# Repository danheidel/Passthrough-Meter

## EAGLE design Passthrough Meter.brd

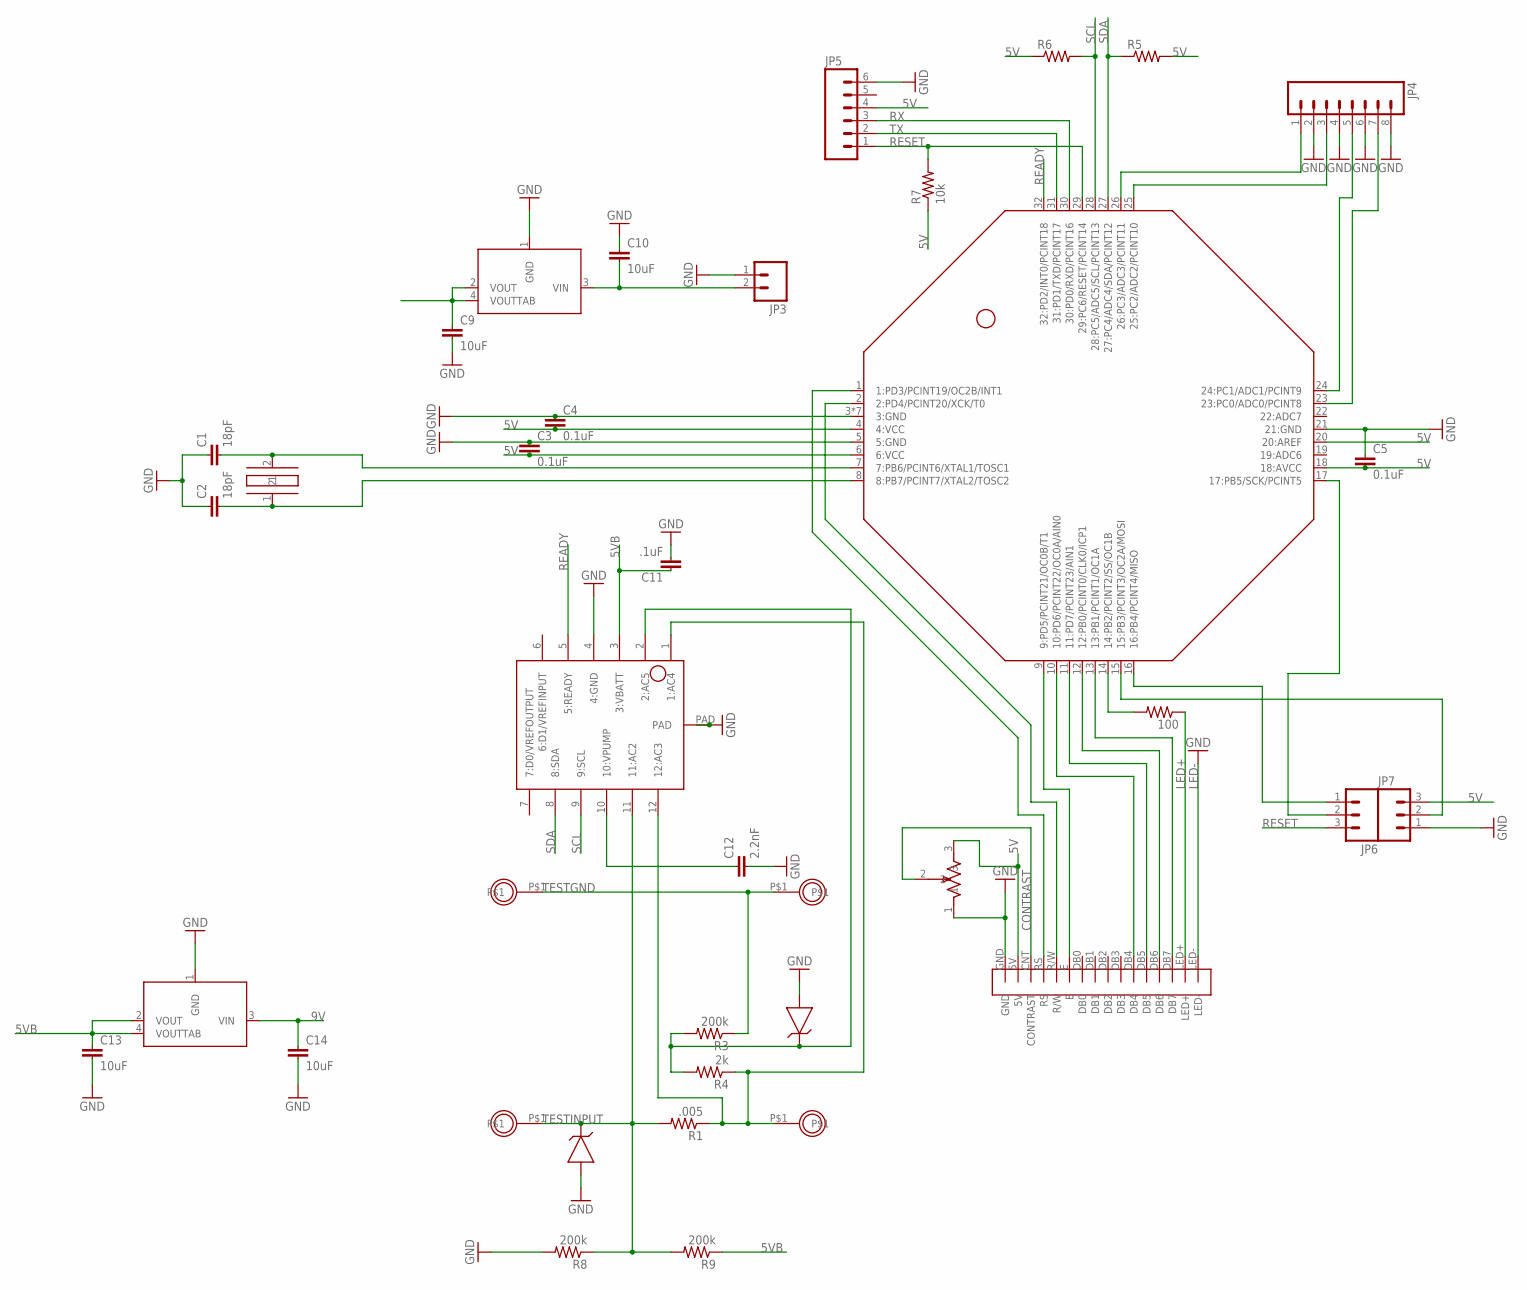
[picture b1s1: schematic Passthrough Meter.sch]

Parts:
100: RESISTOR; 0805
C1, C2: 18pF; 0603-CAP
C3, C4, C5: 0.1uF; 0805
C9, C10, C13, C14: 10uF; 1206
C11: .1uF; 0805
C12: 2.2nF; 0805
JP3: M02LOCK; 1X02_LOCK
JP4: M08LOCK; 1X08_LOCK
JP5: M06LOCK; 1X06_LOCK
JP6, JP7: M03LOCK; 1X03_LOCK
R1: .005; OAR5
R3, R8, R9: 200k; PRECISION-R1
R4: 2k; 0805
R5, R6: RESISTOR; 0805
R7: 10k; 0805
U$1: HC49US
U$3: ATMEGA328SMD-QFN; QFN-32
U$4: SX8723; MPLD-W-12-4X4
U$5, U$15: ZENER_DIODE-SOD-323; SOD-323
U$6: TRIMPOTTC33X-2; TC33X-2
U$7, U$8, U$9, U$10: THROUGH_HOLE-3MM; THROUGH_HOLE_2.2MM
U$13, U$14: 5V-LDO-ZLDO1117; ZLDO1117
U$16: LCD

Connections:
5V: C3.2, C4.2, C5.2, C9.1, JP5.4, JP7.3, R5.2, R6.1, R7.1, U$3.4 (4:VCC), U$3.6 (6:VCC), U$3.18 (18:AVCC), U$3.20 (20:AREF), U$6.3, U$13.2 (VOUT), U$13.4 (VOUTTAB), U$16.5V
5VB: C11.1, C13.1, R9.1, U$4.3 (3:VBATT), U$14.2 (VOUT), U$14.4 (VOUTTAB)
9V: C10.2, C14.1, JP3.2, U$13.3 (VIN), U$14.3 (VIN)
A0: JP4.7, U$3.23 (23:PC0/ADC0/PCINT8)
A1: JP4.5, U$3.24 (24:PC1/ADC1/PCINT9)
A2: JP4.3, U$3.25 (25:PC2/ADC2/PCINT10)
A3: JP4.1, U$3.26 (26:PC3/ADC3/PCINT11)
CONTRAST: U$6.2, U$16.CNT (CONTRAST)
DB7: JP7.2, U$3.15 (15:PB3/PCINT3/OC2A/MOSI)
GND: C1.1, C2.1, C3.1, C4.1, C5.1, C9.2, C10.1, C11.2, C12.2, C13.2, C14.2, JP3.1, JP4.2, JP4.4, JP4.6, JP4.8, JP5.6, JP7.1, R8.2, U$3.3 (3:GND), U$3.5 (5:GND), U$3.21 (21:GND), U$3.P1 (3:GND), U$3.P2 (3:GND), U$3.P3 (3:GND), U$3.P4 (3:GND), U$3.P5 (3:GND), U$3.PAD (3:GND), U$4.4 (4:GND), U$4.PAD, U$5.2 (A), U$6.1, U$13.1 (GND), U$14.1 (GND), U$15.2 (A), U$16.GND
LED+: 100.1, U$16.LED+
LED-: U$16.LED-
MISO: JP6.1, U$3.16 (16:PB4/PCINT4/MISO)
unnamed: C2.2, U$1.1, U$3.8 (8:PB7/PCINT7/XTAL2/TOSC2)
unnamed: C1.2, U$1.2, U$3.7 (7:PB6/PCINT6/XTAL1/TOSC1)
unnamed: 100.2, U$3.14 (14:PB2/PCINT2/SS/OC1B)
unnamed: U$3.13 (13:PB1/PCINT1/OC1A), U$16.DB7
unnamed: U$3.12 (12:PB0/PCINT0/CLK0/ICP1), U$16.DB6
unnamed: U$3.11 (11:PD7/PCINT23/AIN1), U$16.DB5
unnamed: U$3.10 (10:PD6/PCINT22/OC0A/AIN0), U$16.DB4
unnamed: U$3.9 (9:PD5/PCINT21/OC0B/T1), U$16.E
unnamed: U$3.2 (2:PD4/PCINT20/XCK/T0), U$16.R/W
unnamed: U$3.1 (1:PD3/PCINT19/OC2B/INT1), U$16.RS
unnamed: C12.1, U$4.10 (10:VPUMP)
unnamed: R3.2, R4.2, U$4.2 (2:AC5), U$5.1 (C)
READY: U$3.32 (32:PD2/INT0/PCINT18), U$4.5 (5:READY)
RESET: JP5.1, JP6.3, R7.2, U$3.29 (29:PC6/RESET/PCINT14)
RX: JP5.3, U$3.30 (30:PD0/RXD/PCINT16)
SCK: JP6.2, U$3.17 (17:PB5/SCK/PCINT5)
SCL: R6.2, U$3.28 (28:PC5/ADC5/SCL/PCINT13), U$4.9 (9:SCL)
SDA: R5.1, U$3.27 (27:PC4/ADC4/SDA/PCINT12), U$4.8 (8:SDA)
TESTGND: R3.1, U$7.P$1, U$8.P$1
TESTINPUT: R1.2, R8.1, R9.2, U$4.11 (11:AC2), U$9.P$1, U$15.1 (C)
TESTOUTPUT: R1.1, R4.1, U$4.1 (1:AC4), U$4.12 (12:AC3), U$10.P$1
TX: JP5.2, U$3.31 (31:PD1/TXD/PCINT17)

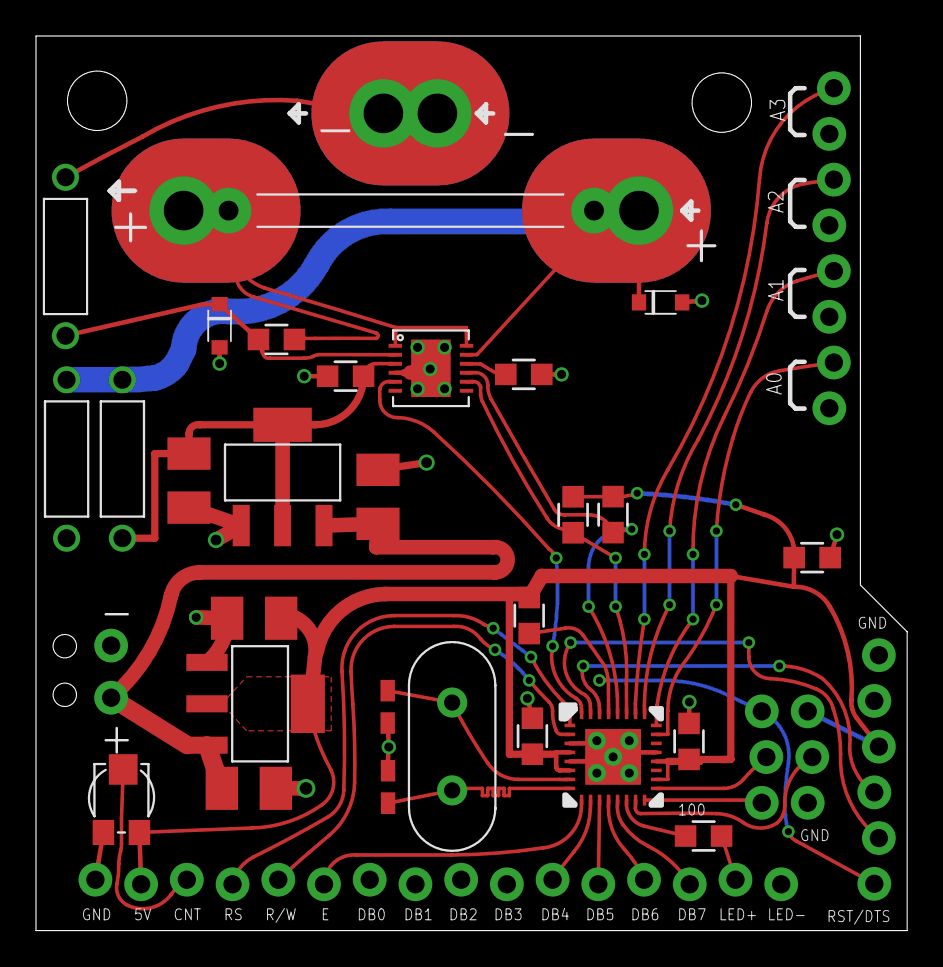
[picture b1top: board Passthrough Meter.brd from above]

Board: 2 copper layers, 48.4 x 49.7 mm, 40 parts (0 on the bottom side), 34 nets.

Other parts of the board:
U$11, U$12: STAND-OFF

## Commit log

2011-06-01 1st commit
2011-08-19 error?
2011-11-22 Lots of changes, this is version sent off for first board run.
2011-12-01 Resized power holes for 12 AWG solid wire, moved them closer to merge soldermask offset so soler can bridge between wires & current resistor to lower extraneous resistance. Changed PS to the correct 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
2011-12-16 Major changes, now changed to new version of ADC, large clean up of trace placement, changed resistors to larger voltage standoff throughholes, overvoltage protection diodes, whole board now floats w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
2011-12-24 File cleanup - deleted Eagle backup files - other minor edits
2011-12-24 Changed creme files to have _creme suffix.
2012-03-16 Updated cream .eps for smaller pads.
2012-03-16 fixed line width.
2012-03-17 Added paste .eps file
2012-04-26 .eps tweaks
2012-04-26 fixup! .eps tweaks
2012-05-22 Major revision
    Removed voltage reference, redid much of the board for better noise and lower BOM.
